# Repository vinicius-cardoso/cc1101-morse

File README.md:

# CC1101 Morse

A handheld Morse transceiver. Key it and the characters go out over 433 MHz;
leave it idle and it decodes what another unit sends back.

Press the key. The device times your dots and dashes, sounds a sidetone so you
hear what you send, keys the CC1101 in step, and prints the decoded letter over
serial. Point a second one at it and the two talk to each other.

The design goal is a board simple enough to make at home: **single layer,
through-hole only, no jumper wires**. There is no display — output is the buzzer
and the serial monitor — and that constraint is what keeps everything else
small.

## Why it is simple

What the board carries is one module on a socket, a button, a buzzer, two
capacitors, two test points and two breakout headers — plus the MCU. None of it
surface-mount. That routes on a single face with no crossings to resolve.

| | |
|---|---|
| Layers | **1** |
| Vias | **0** |
| SMD parts | **0** |
| Jumper wires | **0** |
| Parts to solder | **11** |
| Display | serial + buzzer |

Zero SMD means the board can be hand-soldered from the underside with a plain
iron, and the fiber laser only ever etches one face — no two-sided
registration.

## Hardware

| Part | Role |
|---|---|
| ESP32-C3 Supermini | the brain — timing, decoding, radio, everything |
| CC1101 module | 433 MHz transceiver, socketed |
| Momentary key | Morse input |
| Passive buzzer | sidetone on transmit, audio on receive |
| SSD1306 OLED | *optional* — decoded text, plugs into `J2` |

Everything runs at **3.3 V**. The CC1101 is natively 3.3 V and so is the
ESP32-C3, so the supply is just the Supermini's onboard regulator — no boost
converter, no level shifter, no charge circuit.

### Pin budget — 8 of 13 GPIOs

| Function | Pins |
|---|---|
| CC1101 (SCK, MISO, MOSI, CS, GDO0, GDO2) | 6 |
| Morse key | 1 |
| Buzzer | 1 |
| **Total** | **8 — 5 spare** |
| *OLED (I²C, optional, off-board)* | *2 of the 5* |

See `docs/hardware.md` for the wiring detail.

## Transmit and receive

The CC1101 sends Morse as **OOK** — on-off keying, the carrier simply switched on
for a mark and off for a space. That is what Morse *is* on a radio, and it means
the transmitted signal is the key line itself: no packet format, no framing, no
preamble.

Receiving is the same idea backwards. The CC1101 is put in async serial mode,
where GDO0 goes high whenever the carrier is present, and the firmware times that
pin exactly the way it times the key. One decoder serves both directions.

> [!WARNING]
> **Never key the transmitter with the antenna unscrewed.** With nothing to
> radiate into, power reflects back into the PA and can damage it. For bench
> testing without emitting, use a 50 Ω dummy load in place of the whip.

> [!IMPORTANT]
> The legal position for 433 MHz short-range transmission in Brazil (ANATEL) has
> not been researched. Do that before transmitting outside a dummy load — see
> `docs/roadmap.md` phase 4.

## Power

USB-C, from the ESP32-C3 Supermini's own port. No battery, no charger, no boost,
no battery-sense divider — the board has **zero power components**.

Going portable later means wiring a cell and a TP4056 to the Supermini's
`5V`/`GND` pins. Nothing else changes, because nothing on the board wants more
than 3.3 V — so no boost converter is involved.

## On the bench

The prototype, before the PCB exists: ESP32-C3 Supermini, the CC1101 with its
whip screwed on, a microswitch standing in for the key, a buzzer, and an
SSD1306 OLED on GPIO8/GPIO9.

**The OLED is optional.** `docs/decisions.md` §1 chose no display, and §7 kept
GPIO8/GPIO9 free so one could be added anyway; the board now brings them out on
`J2`, a 4-pin socket a module plugs straight into. The firmware supports a
display without requiring one:
`display.cpp` probes the I²C bus at startup, and if nothing answers, every
display call becomes a no-op. One binary runs with a screen and without.

## The board

The CC1101 plugs into `J1`; `SW1` is the key and `BZ1` the buzzer. `C1`
decouples the `+5V` input to the Supermini's regulator, `C2` the `+3V3` rail at
the radio itself, and `TP1`/`TP2` are probe points for `+5V` and ground. `J2` is
a 4-pin socket for an optional display, with `TP3`/`TP4` a wire link that
completes its `+3V3` — see `docs/decisions.md` §14.

All copper is on the **back** — no vias, no front-side traces. The stock is
single-sided, so components sit on the bare face and are soldered on the copper
face, which is the normal way to build through-hole on one layer.

Ground is the pour filling the board rather than a routed net, which is what
makes single layer work: the net that touches every part never has to be
threaded past the others. See `docs/decisions.md` §10.

Four M2 mounting holes, one per corner. Board is 40 × 60 mm.

## Repository layout

```text
.
├── bom/          # bill of materials
├── docs/         # design decisions, hardware notes
├── firmware/     # Arduino sketch (firmware/cc1101-morse/)
├── hardware/     # KiCad project, datasheets
├── mechanical/   # Onshape exports, case STEP/STL
└── media/        # reference images, photos
```

## Toolchain

- **KiCad** for the PCB (`hardware/kicad/`), exported to DXF for the laser —
  see `docs/fabrication.md`
- **Onshape** for the case, exported to `mechanical/`
- **Fiber laser** to engrave the copper
- **Arduino** for firmware (`firmware/cc1101-morse/`)

Keep editable sources as the source of truth: `.kicad_pro`, `.kicad_sch`,
`.kicad_pcb`, `.ino`, native CAD.

Generated manufacturing output lives in `exports/` and **is committed** —
`hardware/kicad/cc1101-morse/exports/` holds the DXF and drill files the laser
takes. They are derivatives, but a repo whose point is that you can make the
board should carry what the machine eats, without needing KiCad installed to
get it. Regenerate after any board change: `docs/fabrication.md` has the
commands.

## Status

**PCB done.** Routed by hand on one layer, no vias, ground poured — all copper
on the back, since the laminate is single-sided. DRC clean: 0 unconnected,
0 parity errors. DXF and drill files are exported for the laser; see
`docs/fabrication.md`, and **mind the mirror**. Not etched yet.

**The radio works.** On the breadboard the CC1101 answers over SPI
(`PARTNUM 0x0`, `VERSION 0x14`), and `send SOS SOS SOS` at 5 wpm was received on
an RTL-SDR in AM at 433.92 MHz. Key, decoder, buzzer and OLED all confirmed.

Next is phase 2 in `docs/roadmap.md` — a second unit, so two boards talk to each
other.

## Licence

GPL-3.0 — see `LICENSE`.

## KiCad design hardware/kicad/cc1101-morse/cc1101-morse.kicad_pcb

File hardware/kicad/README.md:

# KiCad

The KiCad project lives in `cc1101-morse/`, alongside `libraries/`.

`libraries/` holds the ESP32-C3 Supermini symbol and footprint, which the stock
KiCad libraries do not carry. Nothing else is needed from a custom library: the
CC1101 is a
socketed module represented by a generic `Conn_02x04_Odd_Even`, and everything
else is a stock KiCad part.

## Before drawing anything

Two things from `docs/hardware.md` that are easy to get wrong and expensive to
discover late:

1. **Check the CC1101 module's silkscreen** against the pin table in
   `docs/hardware.md` before routing. Pin order varies by module revision, and
   crossing VCC and GND destroys the module — on a board that is already etched.
   Check its **gender** too: the module on hand has male pins, so the board
   carries a female `PinSocket_2x04`. A `PinHeader` footprint has a different
   drill size and will not fit.

2. **This board is single-layer and through-hole only.** That is a design
   constraint, not a default to relax when routing gets awkward. If a net seems
   to need a jumper, the placement is wrong — see `docs/decisions.md` §3. The
   placement rules that make it work:

   - CC1101 socket at the board edge, SMA pointing outward.
   - Supermini directly beside it, so the six-trace SPI bundle is short.
   - Every ground-connected part at the perimeter; ground routes around the edge
     as a trace with short stubs inward, **not** as a pour.

## Footprints

All through-hole. The full table is in `docs/hardware.md` § KiCad reference —
`SW_PUSH_6mm`, `Buzzer_12x9.5RM7.6`, `PinSocket_2x04_P2.54mm_Vertical`,
`PinHeader_1x02_P2.54mm_Vertical`, `C_Disc_D5.0mm_W2.5mm_P5.00mm`.

## What to commit

Sources, not derivatives: `.kicad_pro`, `.kicad_sch`, `.kicad_pcb`, and any local
library files. The `.gitignore` already excludes backups, autosaves, the KiCad 10
`.history/` store, and generated gerbers — put manufacturing output in an
`exports/` directory if it needs keeping.

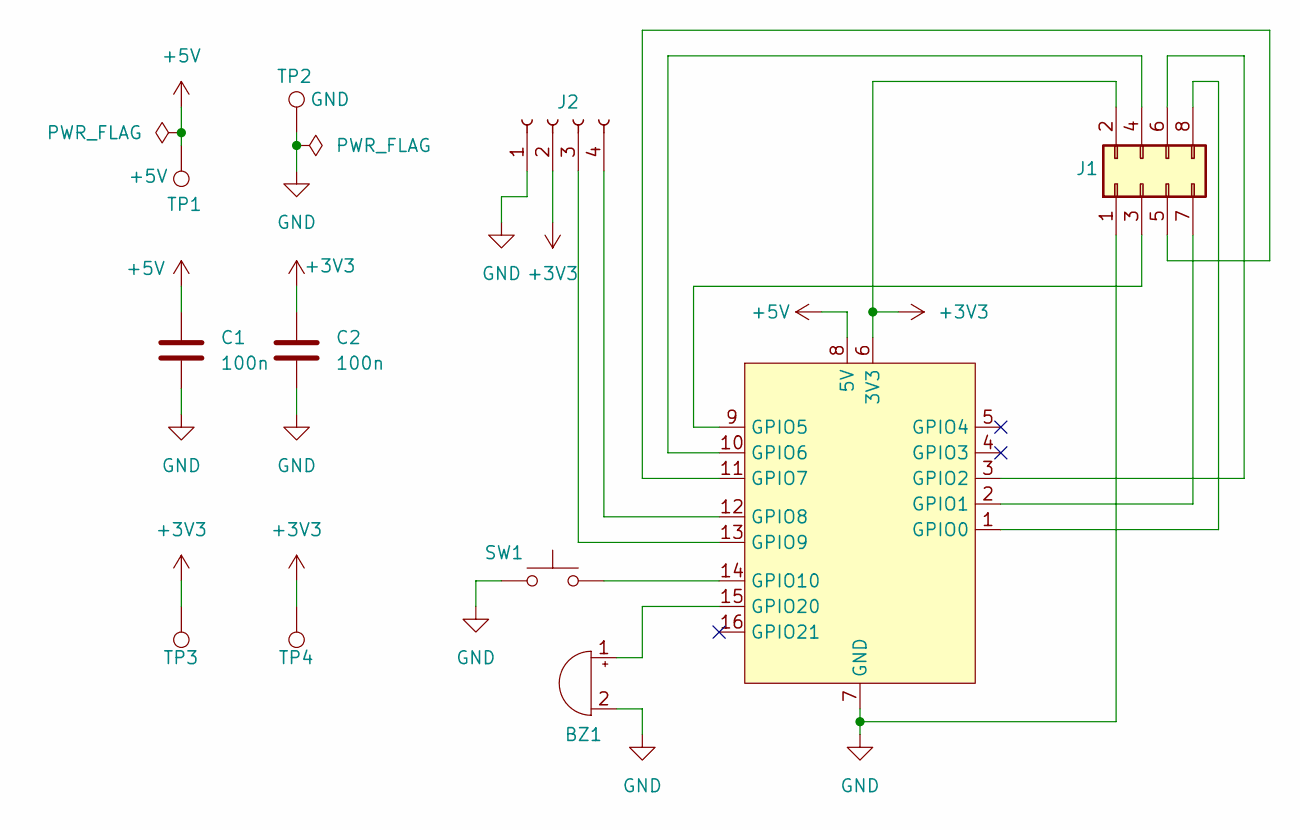
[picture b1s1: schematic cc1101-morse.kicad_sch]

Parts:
BZ1: Buzzer; Buzzer_12x9.5RM7.6
C1, C2: 100n; C_Disc_D5.0mm_W2.5mm_P5.00mm
J1: Conn_02x04_Odd_Even; PinSocket_2x04_P2.54mm_Vertical
J2: Conn_01x04_Socket; PinSocket_1x04_P2.54mm_Vertical
SW1: SW_Push; SW_PUSH_6mm
TP1: +5V; TestPoint_THTPad_2.0x2.0mm_Drill1.0mm
TP2: GND; TestPoint_THTPad_2.0x2.0mm_Drill1.0mm
TP3, TP4: +3V3; TestPoint_THTPad_2.0x2.0mm_Drill1.0mm
U1: ESP32-C3-SuperMini

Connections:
+3V3: C2.1, J1.2, J2.2, TP3.1 (1_1), TP4.1 (1_1), U1.6 (3V3)
+5V: C1.1, TP1.1 (1_1), U1.8 (5V)
GND: BZ1.2 (-), C1.2, C2.2, J1.1, J2.1, SW1.1, TP2.1 (1_1), U1.7 (GND)
unnamed: BZ1.1 (+), U1.15 (GPIO20)
unnamed: J1.3, U1.9 (GPIO5)
unnamed: J1.4, U1.10 (GPIO6)
unnamed: J1.5, U1.11 (GPIO7)
unnamed: J1.6, U1.3 (GPIO2)
unnamed: J1.7, U1.2 (GPIO1)
unnamed: J1.8, U1.1 (GPIO0)
unnamed: J2.3, U1.13 (GPIO9)
unnamed: J2.4, U1.12 (GPIO8)
unnamed: SW1.2, U1.14 (GPIO10)

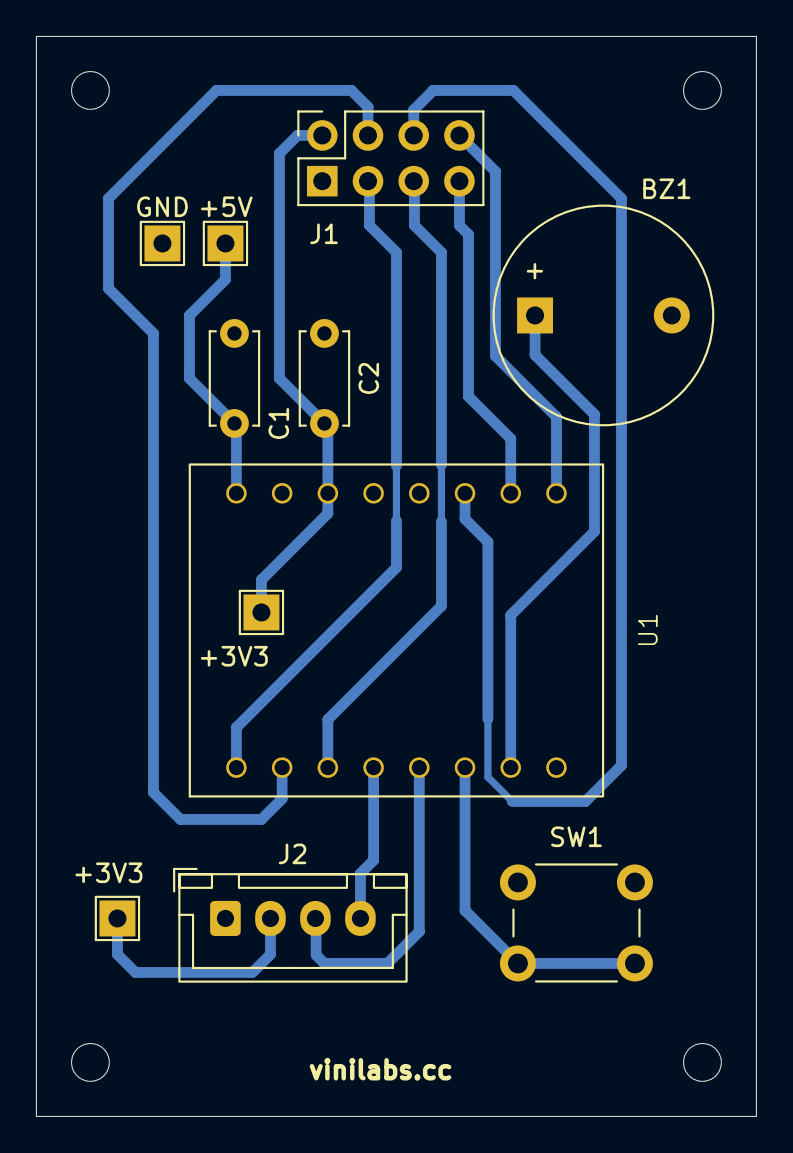
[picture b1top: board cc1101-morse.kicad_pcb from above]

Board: 2 copper layers, 40.0 x 60.0 mm, 15 parts (0 on the bottom side), 13 nets.

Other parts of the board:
H1, H2, H3, H4: MountingHole_2.1mm
